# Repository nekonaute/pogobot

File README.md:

# Pogobot

## Overview 
The pogobot is a small robot designed for swarm robotics experiments, targeted at collective behaviour and social learning research.
The robot is composed of a head (above) with a iCE40UP5K FPGA chip including a softcore processor, an IMU, fast Infra-Red communication devices and a LED.
The head is plugged on a belly (under) which composed of even more LEDs, the motor controler, the battery and the battery regulation system.

To help the understanding, there is two version names used inside the project, one for the hardware and one for the software. <br> 
The following table gives an overview :

| hardware version | software version | comments                                                                             |
|:----------------:|:----------------:|--------------------------------------------------------------------------------------|
|        V3        |        V1        | initial version                                                                      |
|        V3        |        V2        | reduce communication speed to increase reliability                                   |
|        V3        |       V2.1       | reduce header footprint                                                              |
|        V3        |       V2.2       | introduce short message and clean the pogobios                                       |
|        V3        |      V2.2.1      | fix the IR programation problem                                                      |
|        V3        |       V2.3       | API standardization : motor                                                          |
|        V3        |       V2.4       | API standardization : IR messaging                                                   |
|        V3        |       V2.5       | new API standardization : IR messaging                                               |
|        V3        |       V2.6       | new API standardization : IR messaging                                               |
|        V3        |       V2.7       | fix IR saturation at startup, add user access to the flash memory, add magnetometer  |

## Git description
This project is divided into 3 folders :
- Hardware
- Software
- Tools

Hardware contains the schematics and other files to build your own robot from scratch. 

All the schematics were done using KiCad 6. You can find : 
- 'Belly' folder with the belly schematics
- 'Head' folder with the head schematics
- '3d-addons' folder contains all the 3D parts to print to complete a robot
- '3Dmodels' and other folders regroups all the libraries, 3D models and foorprints for KiCad.
   
Software contains the gateware / software / SDK builder in expert mode to upload inside the robot.
It exists 2 softwares inside the robot. 
- The bootloader is the one called when you boot the robot. It contains a gateware and the pogobios.
- The user space is called by a command inside the bootloader. It contains your code and a gateware. <br>
/!\ If you plan to use the pogobot in the user space please use the sdk [here](https://github.com/nekonaute/pogobot-sdk).
  
Tools corresponds to the differents tools used around the robot.

### Shortcuts to

- [Normal mode software](https://github.com/nekonaute/pogobot-sdk)
- [Expert mode software](/Software/readme.md)
- [Hardware](/Hardware/readme.md)
- [Ir Remote software](/readme-irRemote.md)
- [Charger](/Hardware/readme.md)
- [Pogobject](/Software/pogobject/readme.md)
- [PogoWallApp](/Software/pogoWallApp/readme.md)

## Pogobios LED Status

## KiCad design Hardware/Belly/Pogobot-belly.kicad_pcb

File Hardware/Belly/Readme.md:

# Belly
Belly board (Kicad project) to use with head board (pogobot v2).
Holds the battery, battery charger, motors, ...

## Belly v2
file : bellyv2

## Belly V3
file : pogobot_belly

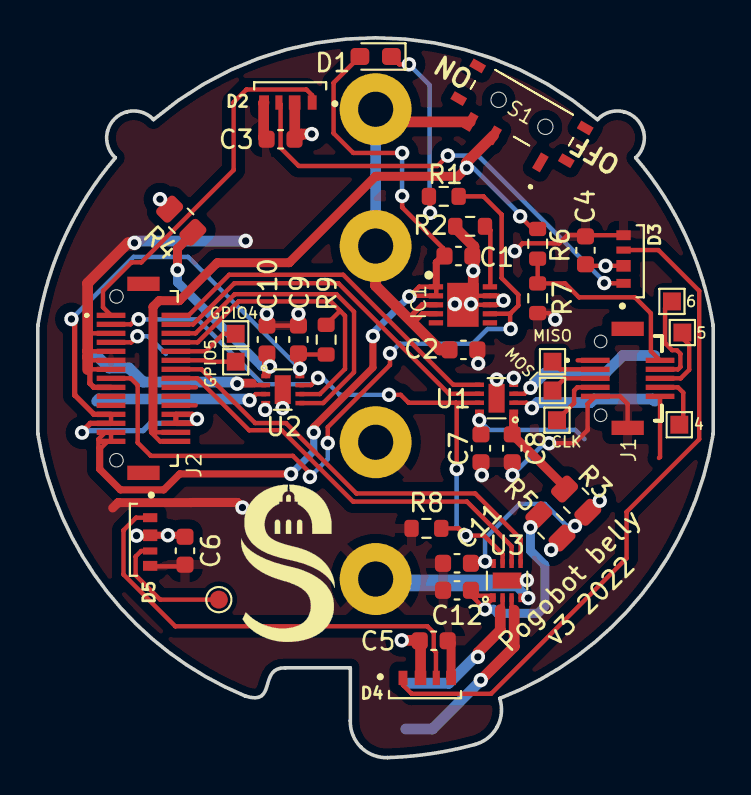
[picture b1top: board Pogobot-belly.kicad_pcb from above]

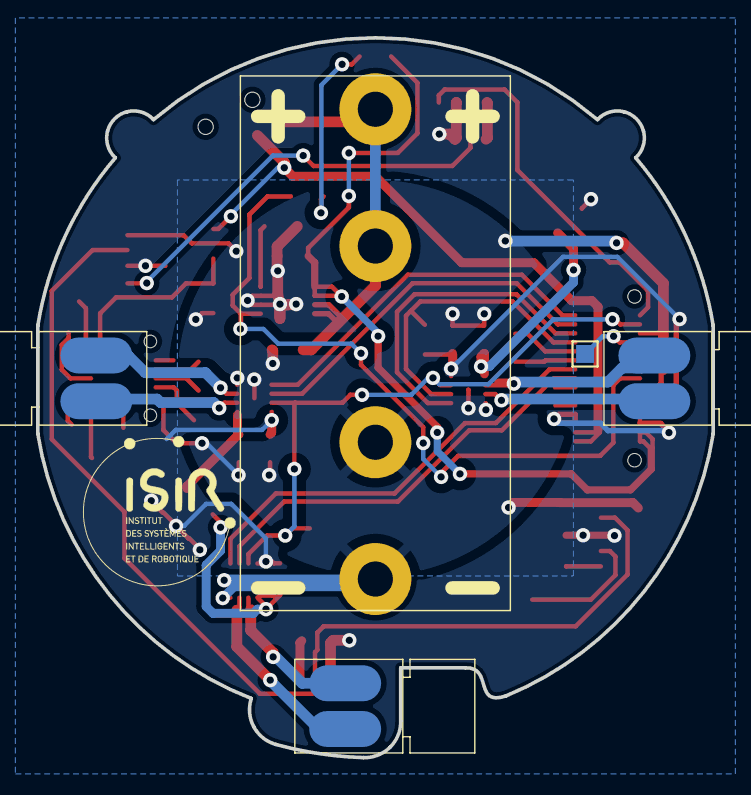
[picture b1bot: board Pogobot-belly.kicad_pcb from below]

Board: 2 copper layers, 37.5 x 40.0 mm, 47 parts (5 on the bottom side), 39 nets.

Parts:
4, 5, 6: TestPoint; TestPoint_Pad_1.0x1.0mm
C1, C2: 4.7uF; C_0603_1608Metric
C3, C4, C5, C6: 1uF; C_0603_1608Metric
C7, C8, C9, C10, C11, C12: 100n; C_0603_1608Metric
CLK: TestPoint; TestPoint_Pad_1.0x1.0mm
D1: LED; LED_0603_1608Metric_Pad1.05x0.95mm_HandSolder
D2, D3, D4, D5: IN-PI42TASPRPGPB; LED_IN-PI42TASPRPGPB
GPIO4, GPIO5: TestPoint; TestPoint_Pad_1.0x1.0mm
IC1: MCP73123-22SI_MF; SON50P300X300X100-11N-D
J1: 10132797-015100LF; 10132797015100LF
J2: 10132797-035100LF; 10132797035100LF
J3: CR2 Battery Holder; CR2_Holder
M1, M2, M3: Motor_DC; Vibrating_5x6mm_DC_motor
MISO: TestPoint; TestPoint_Pad_1.0x1.0mm
MOSI: TestPoint; TestPoint_Pad_1.0x1.0mm
R1: 1K; R_0603_1608Metric
R2, R6, R7, R8, R9: 10K; R_0603_1608Metric
R3, R4, R5: 0; R_0805_2012Metric
S1: MSK12C02
TP1: TestPoint; TestPoint_Pad_1.0x1.0mm
TP4: RGB_Out; TestPoint_Pad_D1.0mm
U1, U2, U3: DRV8837C; WSON-8-1EP_2x2mm_P0.5mm_EP0.9x1.6mm

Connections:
+3V3: C3.1, C4.1, C5.1, C6.1, C7.1, C9.1, C11.1, D2.2 (VDD), D3.2 (VDD), D4.2 (VDD), D5.2 (VDD), J2.12, J2.13, J2.18, J2.19, R3.1, R4.1, R5.1, R9.1, U1.8 (VCC), U2.8 (VCC), U3.8 (VCC)
+5V: C1.1, D1.2 (A), IC1.1 (VDD_1), IC1.2 (VDD_2), J2.14, J2.15
+BATT: J2.16, J2.17, R6.1, S1.B1 (COM)
/CH4: 4.1, J1.7
/CH5: 5.1, J1.8
/CH6: 6.1, J1.9
/CH7: J1.10, R6.2, R7.1
/prog: IC1.10 (PROG), R2.2
CDONE: J2.4, TP1.1
GND: C1.2, C2.2, C3.2, C4.2, C5.2, C6.2, C7.2, C8.2, C9.2, C10.2, C11.2, C12.2, D2.4 (GND), D3.4 (GND), D4.4 (GND), D5.4 (GND), IC1.8 (VSS_1), IC1.9 (VSS_2), IC1.11 (EP), J1.5, J1.MP2, J2.3, J2.5, J2.6, J2.7, J2.9, J3.2, R2.1, R7.2, R8.2, U1.4 (GND), U1.9 (GND), U2.4 (GND), U2.9 (GND), U3.4 (GND), U3.9 (GND)
GPIO0: J2.30, U1.5 (IN2)
GPIO1: J2.29, U1.6 (IN1)
GPIO2: J2.28, U2.5 (IN2)
GPIO3: J2.27, R9.2, U2.6 (IN1)
GPIO4: GPIO4.1, J2.26
GPIO5: GPIO5.1, J2.25
GPIO6: J2.24, U3.5 (IN2)
GPIO7: J2.23, U3.6 (IN1)
GPIO8: J2.2, R8.1, U1.7 (~SLEEP), U2.7 (~SLEEP), U3.7 (~SLEEP)
LED_CHARGE: IC1.7 (STAT), J2.8, R1.2
unnamed: C2.1, IC1.3 (VBAT_1), IC1.4 (VBAT_2), J3.1, S1.C1 (NO)
unnamed: C8.1, R3.2, U1.1 (VM)
unnamed: C10.1, R4.2, U2.1 (VM)
unnamed: C12.1, R5.2, U3.1 (VM)
unnamed: D1.1 (K), R1.1
unnamed: D2.3 (DOUT), D3.1 (DIN)
unnamed: D3.3 (DOUT), D4.1 (DIN)
unnamed: D4.3 (DOUT), D5.1 (DIN)
unnamed: D5.3 (DOUT), TP4.1
unnamed: M1.1 (+), U1.2 (OUT1)
unnamed: M1.2 (-), U1.3 (OUT2)
unnamed: M2.1 (+), U2.2 (OUT1)
unnamed: M2.2 (-), U2.3 (OUT2)
unnamed: M3.1 (+), U3.2 (OUT1)
unnamed: M3.2 (-), U3.3 (OUT2)
RGB_LED_OUT: D2.1 (DIN), J2.1
SPI_CLK: CLK.1, J1.4
SPI_MISO: J1.2, MISO.1
SPI_MOSI: J1.3, MOSI.1

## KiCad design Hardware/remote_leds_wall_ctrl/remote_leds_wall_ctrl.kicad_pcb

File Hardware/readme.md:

# Hardware
Here you can find the description and information for each part developped.

<!-- vscode-markdown-toc -->
- [Hardware](#hardware)
  - [Folder description](#folder-description)
  - [Pogobot robot](#pogobot-robot)
    - [Hardware schematic](#hardware-schematic)
    - [What's needed for 1 robot](#whats-needed-for-1-robot)
    - [Motor information](#motor-information)
    - [3d printed parts](#3d-printed-parts)
      - [Printing info](#printing-info)
      - [Assembly](#assembly)
  - [USB UART progboard](#usb-uart-progboard)
  - [Charger](#charger)
  - [IR remote](#ir-remote)
  - [IR Wall](#ir-wall)
  - [Pogobject](#pogobject)

<!-- vscode-markdown-toc-config
	numbering=false
	autoSave=true
	/vscode-markdown-toc-config -->
<!-- /vscode-markdown-toc -->

## Folder description
In this folder, you can find 3d models and kicad files.

The folder :
- "3d-addons" contains all the STL files to build the different object.
- "3Dmodels" contains the 3D models for Kicad
- 'Belly" contains the kicad files for the belly
- "Charger" contains the kicad files for the charger
- "Footprints.pretty" is the Kicad library for custom footprints
- "Head" contains the kicad files for the head
- "pogo_object" contains the kicad files for the pogobject
- "remote" contains the kicad files for the board which host the head of a remote
- "remote_leds_strip" contains the kicad files for the "shower" part of a remote
- "remote_leds_wall_ctrl" contains the kicad files for the amplification signal for a led strip
- "remote_leds_wall_strip" contains the kicad files for the strip leds of a wall remote
- "Symbols" contains the custom symbols for kicad
- "usb-uart-progboard" contains the kicad files for the programmation board by cable

## Pogobot robot

### Hardware schematic
Here you can find the global view of the hardware.

### What's needed for 1 robot

In order to complete a robot, you will need : 
- a belly and a head
- a 3v CR2 rechargeable Batery (Li-FePO4)
- 3 motors
- the different 3d printed parts

### Motor information
All the models are designed for the motors available here:
<!-- https://www.aliexpress.com/item/32918768766.html old ref -->
https://www.ebay.com/itm/115374108208

### 3d printed parts
All the parts are available inside the folder 'Hardware/3d-addons'.

#### Printing info
The different models have been printed in PLA with an Ultimaker2+ with a layer height of 0.2mm without support or brim.

To assemble a robot, you need to print a skirt, a capsule and a hat for the version of your belly. <br>
After printed the capsule, you have to set free the tabs by gently cut under.

HINT: The hat has to be returned to be printed without support.

#### Assembly
- First, place the motors inside the 3 holes.
- Then, place the robot inside the capsule.
- Finally, place the robot+capsule inside the skirt.

## USB UART progboard
In order to program the robot by cable, you need a USB to UART device connected between your computor and the FFC/FPC connector on the head. 
The folder 'Hardware/usb-uart-progboard' contains the Kicad files to produce a small board to program the robot. 
You also need :
- UMFT234XF board (https://www.mouser.fr/ProductDetail/FTDI/UMFT234XF?qs=NVftvxkm2thPJLzIkoAhbA%3D%3D)
- a FFC/FPC connector (8 pins, 0.5 mm, SMD/SMT, Right Angle, Dual Contact) like https://www.mouser.fr/ProductDetail/571-2328702-8
- a FFC/FPC cable (8 pins, 0.5 mm) like https://www.mouser.fr/ProductDetail/538-15166-0087
- a USB micro => USB cable

## Charger
There is two ways to recharge a pogobot:
- by the programming cable
- by the plus and minus pads on the head

In order to charge multiple robot at once, we develop a charger using pogopins that connect the plus and minus on the head of the robot by flipping the robot.

The PCB cad files are available in the folder.
The pogopin used are these : https://www.digikey.fr/en/products/detail/preci-dip/90224-AS/5451911
We also used one power jack 5.1 embase connected to the power outlet. The second one is used, if you want to daisy chain multiple PCB (be careful, the total amps used).
:warning: The power plug has to expose the +5v on the inner contact and Ground on the outer contact. Please verify with a voltmeter before pluggin a robot.

We developed some small feet to mount with M3 screws on the PCB and some small cones in order to help the contacts for each robot.
Both 3d designs are available in the folder "3d-addons" (pogocharger*).

## IR remote
2 types of IR remote are possible. A small one and one with a shower. 

The small one is combination of a pogobot head + usb-uart-progboard + 3D structure (pogoremote_down.stl + pogoremote_up.stl) + 2 M3x10mm screws.

The big one is combination of a pogobot head + remote + remote_Leds_strip + 3D structure

The leds are TSAL6200.

This version can use the USB alimentation or an external one (up to 12v) to extend the range of the remote. The jumper near the power jack determine the origin of the tension for the Leds.

## IR Wall 

The IR wall is a modified remote that can connect a long strip of Leds.
We didn't manage to find the correct Led strip for our application so we designed a strip led (remote_leds_wall_strip) that was produiced on flexible pcb. 

To produice a IR wall, you need a pogobot head + remote + remote_leds_wall_ctrl + remote_leds_wall_strip. 

The leds are VSM3940x01.

## Pogobject

The pogobject is composed of a dfrobot firebeatle + pogobot head + pogo_object PCB. Through WIFI, it can be possible to send command to the pogobot head and so to change the message send by the object.

The pogobject is a large PCB that contains all the electronics. It is placed inside a 3d printed structure. This structure is placed on 4 caster with metal ball (pololu item 953) in order to be pushed by the robot. To make it fixed a aluminum weight is used to held it in place. 

The leds are TSAL6200.

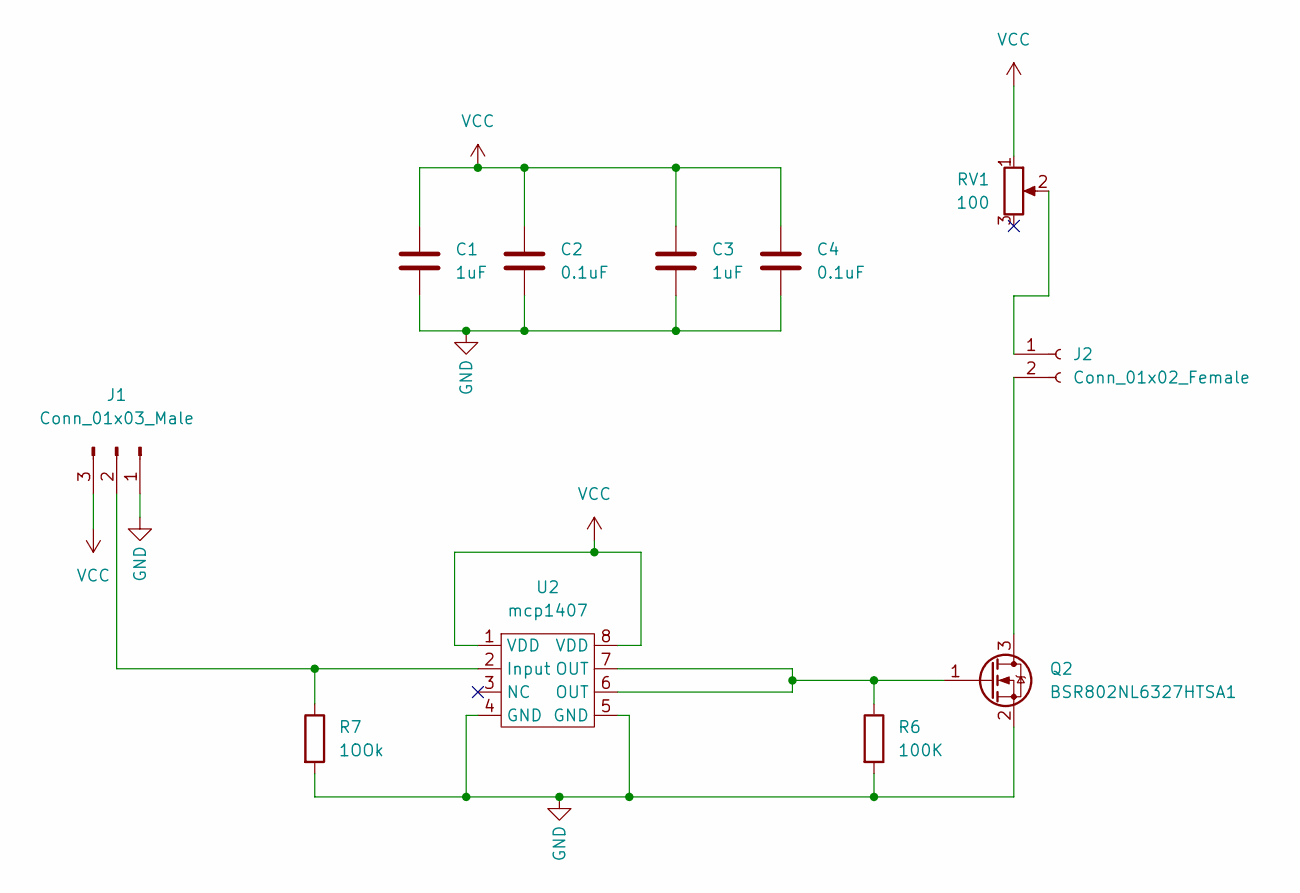
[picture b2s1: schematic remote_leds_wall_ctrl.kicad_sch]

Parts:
C1: 1uF; C_0805_2012Metric_Pad1.18x1.45mm_HandSolder
C2: 0.1uF; C_0805_2012Metric_Pad1.18x1.45mm_HandSolder
C3: 1uF; CP_Radial_D5.0mm_P2.00mm
C4: 0.1uF; CP_Radial_D5.0mm_P2.00mm
J1: Conn_01x03_Male; PinHeader_1x03_P2.54mm_Vertical
J2: Conn_01x02_Female; PinHeader_1x02_P2.54mm_Vertical
Q2: BSR802NL6327HTSA1; SOT-23
R6: 100K; R_0805_2012Metric_Pad1.20x1.40mm_HandSolder
R7: 1OOk; R_0805_2012Metric_Pad1.20x1.40mm_HandSolder
RV1: 100; PinHeader_1x03_P2.54mm_Vertical
U2: mcp1407; SOIC-8_3.9x4.9mm_P1.27mm

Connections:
GND: C1.2, C2.2, C3.2, C4.2, J1.1, Q2.2 (S), R6.2, R7.2, U2.4 (GND), U2.5 (GND)
unnamed: J1.2, R7.1, U2.2 (Input)
unnamed: J2.1, RV1.2
unnamed: J2.2, Q2.3 (D)
unnamed: Q2.1 (G), R6.1, U2.6 (OUT), U2.7 (OUT)
VCC: C1.1, C2.1, C3.1, C4.1, J1.3, RV1.1, U2.1 (VDD), U2.8 (VDD)

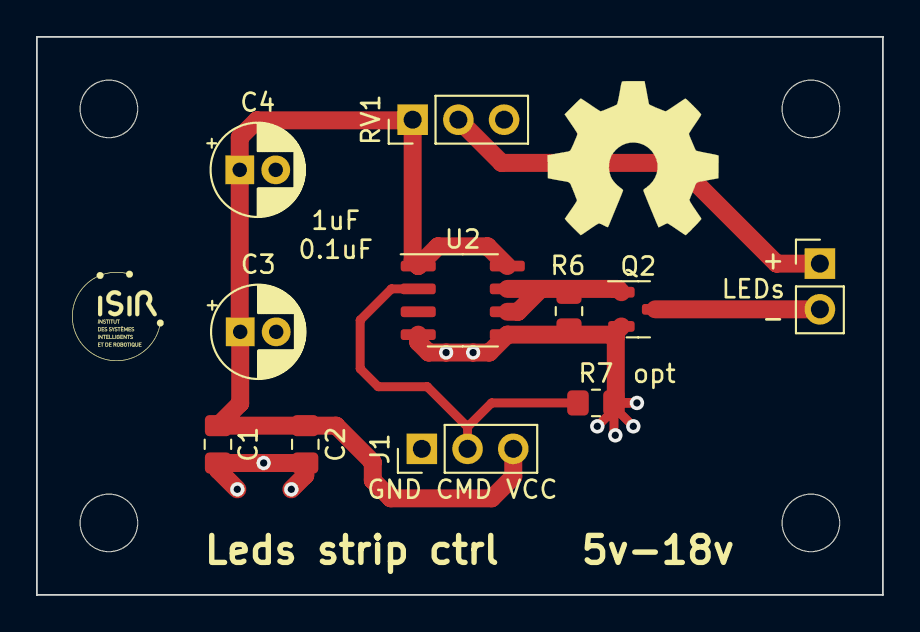
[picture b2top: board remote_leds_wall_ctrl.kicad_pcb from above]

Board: 2 copper layers, 47.0 x 31.0 mm, 11 parts (0 on the bottom side), 6 nets.

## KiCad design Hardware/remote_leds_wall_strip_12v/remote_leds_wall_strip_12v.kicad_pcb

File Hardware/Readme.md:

# Hardware
Here you can find the description and information for each part developped.

<!-- vscode-markdown-toc -->
- [Hardware](#hardware)
  - [Folder description](#folder-description)
  - [Pogobot robot](#pogobot-robot)
    - [Hardware schematic](#hardware-schematic)
    - [What's needed for 1 robot](#whats-needed-for-1-robot)
    - [Motor information](#motor-information)
    - [3d printed parts](#3d-printed-parts)
  - [USB UART progboard](#usb-uart-progboard)
  - [Charger](#charger)
  - [IR remote](#ir-remote)
  - [IR Wall](#ir-wall)
  - [Pogobject](#pogobject)

<!-- vscode-markdown-toc-config
	numbering=false
	autoSave=true
	/vscode-markdown-toc-config -->
<!-- /vscode-markdown-toc -->

## Folder description
In this folder, you can find 3d models and kicad files.

The folder :
- "3Dmodels" contains the 3D models for Kicad
- 'Belly" contains the kicad files for the belly
- "Charger" contains the kicad files for the charger
- "Footprints.pretty" is the Kicad library for custom footprints
- "Head" contains the kicad files for the head
- "pogo_object" contains the kicad files for the pogobject
- "remote" contains the kicad files for the board which host the head of a remote
- "remote_leds_strip" contains the kicad files for the "shower" part of a remote
- "remote_leds_wall_ctrl" contains the kicad files for the amplification signal for a led strip
- "remote_leds_wall_strip" contains the kicad files for the strip leds of a wall remote
- "Symbols" contains the custom symbols for kicad
- "usb-uart-progboard" contains the kicad files for the programmation board by cable

## Pogobot robot

### Hardware schematic
Here you can find the global view of the hardware.

### What's needed for 1 robot

In order to complete a robot, you will need : 
- a belly and a head
- a 3v CR2 rechargeable Batery (Li-FePO4)
- 3 motors
- the different 3d printed parts

### Motor information
All the models are designed for the motors available here:
<!-- https://www.aliexpress.com/item/32918768766.html old ref -->
https://www.ebay.com/itm/115374108208

### 3d printed parts
All the parts are available inside the folder '3d-addons', along with [assembly instructions](../3d-addons/Readme.md).

## USB UART progboard
In order to program the robot by cable, you need a USB to UART device connected between your computor and the FFC/FPC connector on the head. 
The folder 'Hardware/usb-uart-progboard' contains the Kicad files to produce a small board to program the robot. 
You also need :
- UMFT234XF board (https://www.mouser.fr/ProductDetail/FTDI/UMFT234XF?qs=NVftvxkm2thPJLzIkoAhbA%3D%3D)
- a FFC/FPC connector (8 pins, 0.5 mm, SMD/SMT, Right Angle, Dual Contact) like https://www.mouser.fr/ProductDetail/571-2328702-8
- a FFC/FPC cable (8 pins, 0.5 mm) like https://www.mouser.fr/ProductDetail/538-15166-0087
- a USB micro => USB cable

## Charger
There is two ways to recharge a pogobot:
- by the programming cable
- by the plus and minus pads on the head

In order to charge multiple robot at once, we develop a charger using pogopins that connect the plus and minus on the head of the robot by flipping the robot.

The PCB cad files are available in the folder.
The pogopin used are these : https://www.digikey.fr/en/products/detail/preci-dip/90224-AS/5451911
We also used one power jack 5.1 embase connected to the power outlet. The second one is used, if you want to daisy chain multiple PCB (be careful, the total amps used).
:warning: The power plug has to expose the +5v on the inner contact and Ground on the outer contact. Please verify with a voltmeter before pluggin a robot.

We developed some small feet to mount with M3 screws on the PCB and some small cones in order to help the contacts for each robot.
Both 3d designs are available in the folder "3d-addons" (pogocharger*).

## IR remote
2 types of IR remote are possible. A small one and one with a shower. 

The small one is combination of a pogobot head + usb-uart-progboard + 3D structure (pogoremote_down.stl + pogoremote_up.stl) + 2 M3x10mm screws.

The big one is combination of a pogobot head + remote + remote_Leds_strip + 3D structure

The leds are TSAL6200.

This version can use the USB alimentation or an external one (up to 12v) to extend the range of the remote. The jumper near the power jack determine the origin of the tension for the Leds.

## IR Wall 

The IR wall is a modified remote that can connect a long strip of Leds.
We didn't manage to find the correct Led strip for our application so we designed a strip led (remote_leds_wall_strip) that was produiced on flexible pcb. 

To produice a IR wall, you need a pogobot head + remote + remote_leds_wall_ctrl + remote_leds_wall_strip. 

The leds are VSM3940x01.

## Pogobject

The pogobject is composed of a dfrobot firebeatle + pogobot head + pogo_object PCB. Through WIFI, it can be possible to send command to the pogobot head and so to change the message send by the object.

The pogobject is a large PCB that contains all the electronics. It is placed inside a 3d printed structure. This structure is placed on 4 caster with metal ball (pololu item 953) in order to be pushed by the robot. To make it fixed a aluminum weight is used to held it in place. 

The leds are TSAL6200.

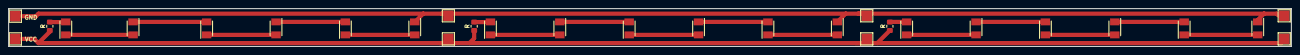
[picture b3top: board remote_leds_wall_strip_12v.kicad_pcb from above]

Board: 2 copper layers, 305.1 x 9.0 mm, 29 parts (0 on the bottom side), 20 nets.

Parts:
L1, L2, L3, L4, L5, L6, L7, L8, L9, L10, L11, L12, L13, L14, L15, L16, L17, L18: VSMB3940X01-GS08; LEDM3528X185N
R: 15; R_0805_2012Metric_Pad1.20x1.40mm_HandSolder
R#2, R#3: 15; R_0805_2012Metric_Pad1.20x1.40mm_HandSolder
TP1, TP2, TP3, TP4, TP5, TP6, TP12, TP27: TestPoint; TestPoint_Pad_2.5x2.5mm

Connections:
GND: L4.1 (K), L10.1 (K), L16.1 (K), TP1.1, TP3.1, TP6.1, TP12.1
unnamed: L1.1 (K), L2.2 (A)
unnamed: L1.2 (A), L18.1 (K)
unnamed: L2.1 (K), L3.2 (A)
unnamed: L3.1 (K), L4.2 (A)
unnamed: L5.1 (K), L6.2 (A)
unnamed: L5.2 (A), R#3.2
unnamed: L6.1 (K), L7.2 (A)
unnamed: L7.1 (K), L8.2 (A)
unnamed: L8.1 (K), L9.2 (A)
unnamed: L9.1 (K), L10.2 (A)
unnamed: L11.1 (K), L12.2 (A)
unnamed: L11.2 (A), R.2
unnamed: L12.1 (K), L13.2 (A)
unnamed: L13.1 (K), L14.2 (A)
unnamed: L14.1 (K), L15.2 (A)
unnamed: L15.1 (K), L16.2 (A)
unnamed: L17.1 (K), L18.2 (A)
unnamed: L17.2 (A), R#2.2
VCC: R.1, R#2.1, R#3.1, TP2.1, TP4.1, TP5.1, TP27.1

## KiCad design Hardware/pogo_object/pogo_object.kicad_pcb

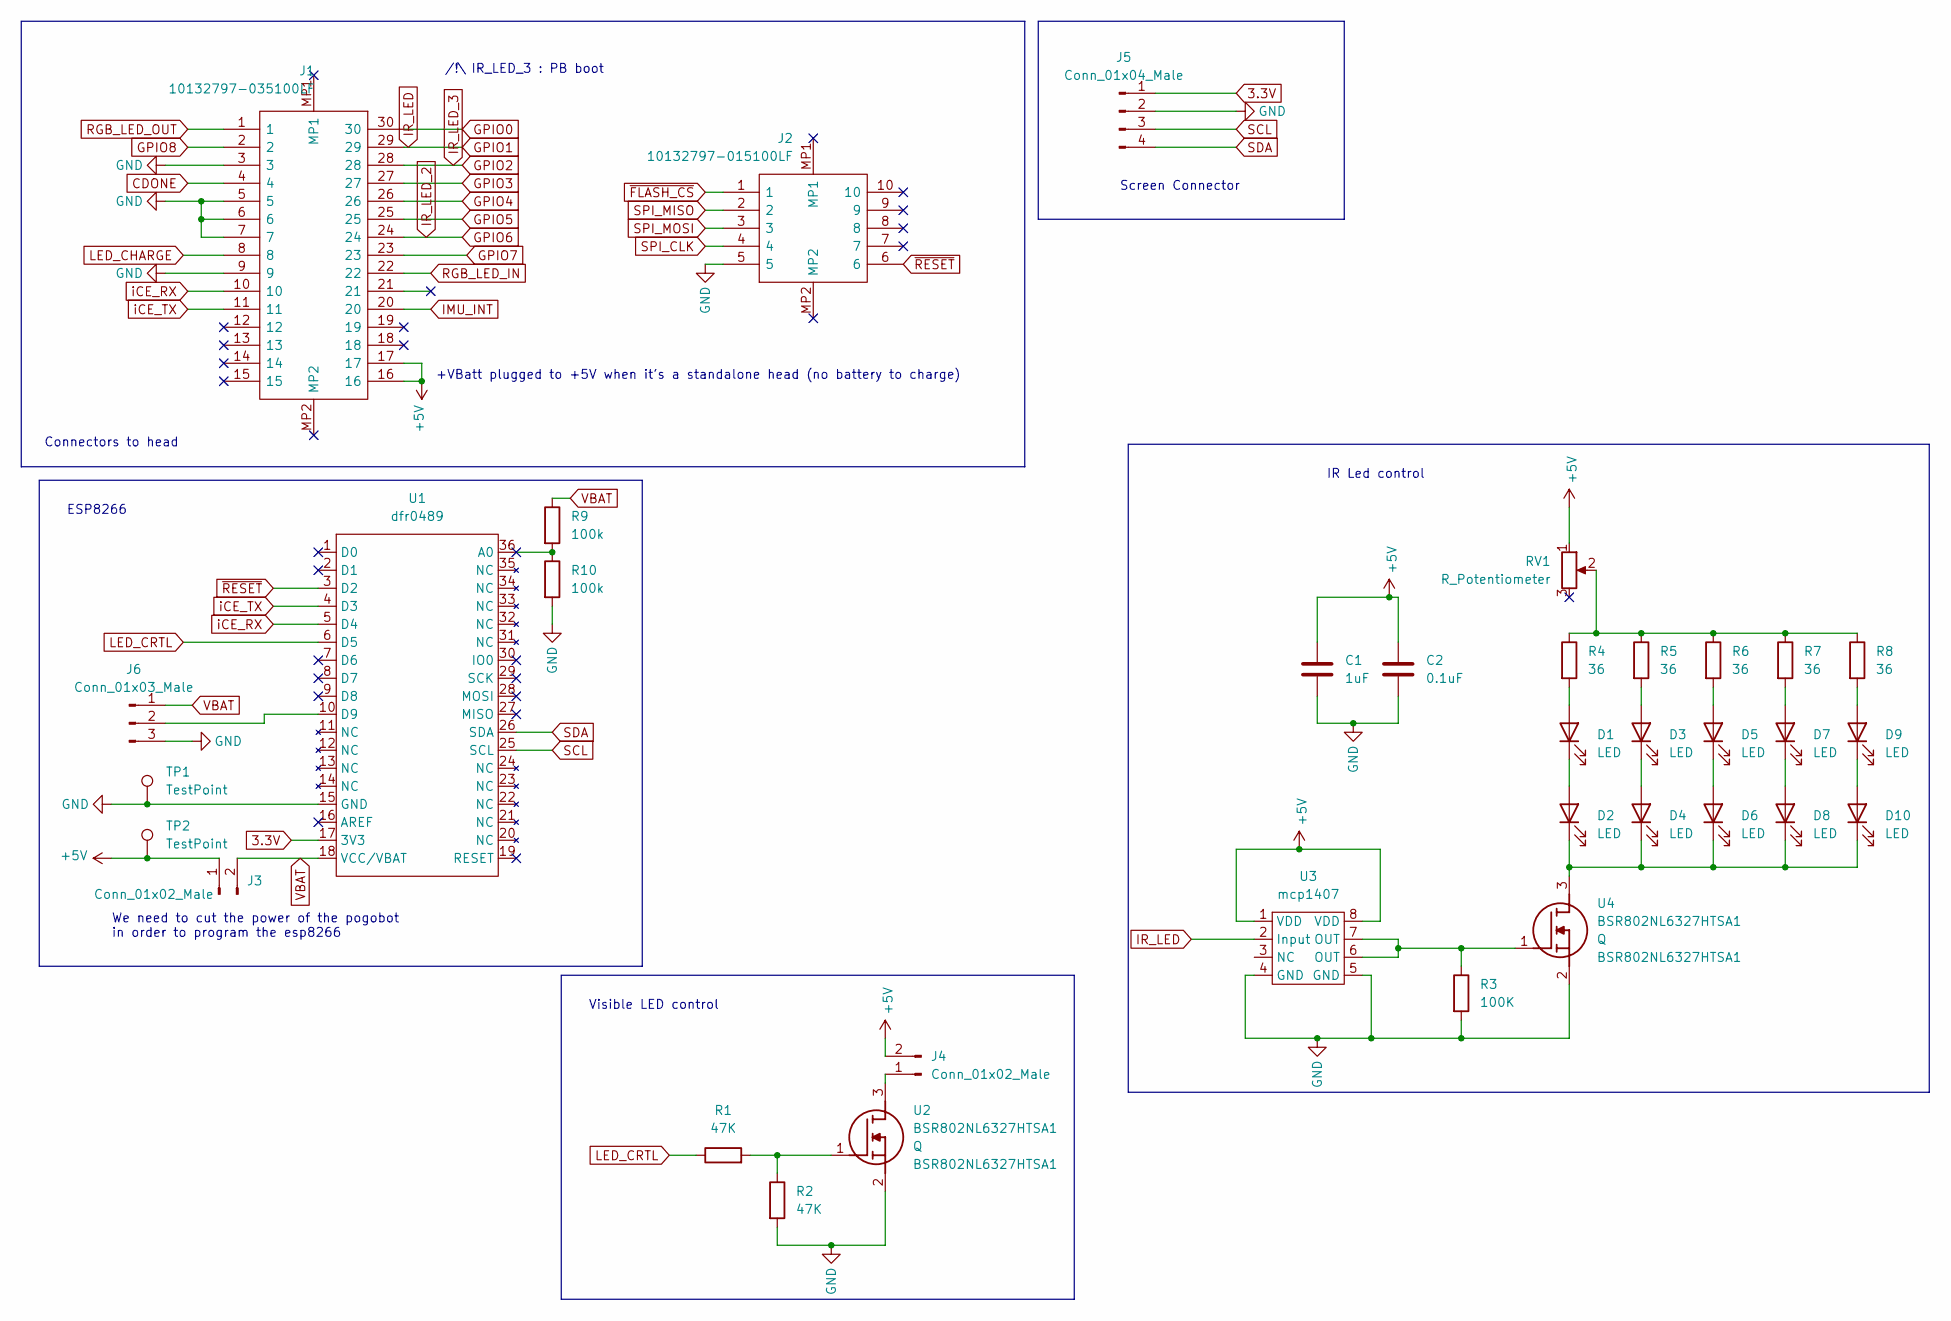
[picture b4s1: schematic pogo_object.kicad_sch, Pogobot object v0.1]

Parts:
C1: 1uF; CP_Radial_D8.0mm_P5.00mm
C2: 0.1uF; CP_Radial_D8.0mm_P5.00mm
D1, D2, D3, D4, D5, D6, D7, D8, D9, D10: LED; D_A-405_P2.54mm_Vertical_AnodeUp
J1: 10132797-035100LF; 10132797035100LF; Manufacturer_Part_Number 10132797-035100LF; Mouser Part Number 649-10132797035100LF
J2: 10132797-015100LF; 10132797015100LF; Manufacturer_Part_Number 10132797-015100LF; Mouser Part Number 649-10132797015100LF
J3, J4: Conn_01x02_Male; PinHeader_1x02_P2.54mm_Vertical
J5: Conn_01x04_Male; PinHeader_1x04_P2.54mm_Vertical
J6: Conn_01x03_Male; PinHeader_1x03_P2.54mm_Vertical
R1, R2: 47K; R_0805_2012Metric_Pad1.20x1.40mm_HandSolder
R3: 100K; R_0805_2012Metric_Pad1.20x1.40mm_HandSolder
R4, R5, R6, R7, R8: 36; R_0805_2012Metric_Pad1.20x1.40mm_HandSolder
R9, R10: 100k; R_0805_2012Metric_Pad1.20x1.40mm_HandSolder
RV1: R_Potentiometer; PinHeader_1x03_P2.54mm_Vertical
TP1, TP2: TestPoint; TestPoint_Pad_3.0x3.0mm
U1: dfr0489
U2, U4: BSR802NL6327HTSA1; SOT95P285X135-3N; Mouser Part Number 726-BSR802NL6327HTSA
U3: mcp1407; SOIC-8_3.9x4.9mm_P1.27mm

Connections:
3.3V: J5.1, U1.17 (3V3)
+5V: C1.1, C2.1, J1.16, J1.17, J3.1, J4.2, RV1.1, TP2.1, U3.1 (VDD), U3.8 (VDD)
CDONE: J1.4
GND: C1.2, C2.2, J1.3, J1.5, J1.6, J1.7, J1.9, J2.5, J5.2, J6.3, R2.2, R3.2, R10.2, TP1.1, U1.15 (GND), U2.2 (S), U3.4 (GND), U3.5 (GND), U4.2 (S)
GPIO0: J1.30
GPIO1: J1.29, U3.2 (Input)
GPIO2: J1.28
GPIO3: J1.27
GPIO4: J1.26
GPIO5: J1.25
GPIO6: J1.24
GPIO7: J1.23
GPIO8: J1.2
IMU_INT: J1.20
LED_CHARGE: J1.8
LED_CRTL: R1.1, U1.6 (D5)
unnamed: D1.1 (K), D2.2 (A)
unnamed: D1.2 (A), R4.2
unnamed: D3.1 (K), D4.2 (A)
unnamed: D3.2 (A), R5.2
unnamed: D5.1 (K), D6.2 (A)
unnamed: D5.2 (A), R6.2
unnamed: D7.1 (K), D8.2 (A)
unnamed: D7.2 (A), R7.2
unnamed: D9.2 (A), R8.2
unnamed: D2.1 (K), D4.1 (K), D6.1 (K), D8.1 (K), D10.1 (K), U4.3 (D)
unnamed: D9.1 (K), D10.2 (A)
unnamed: J4.1, U2.3 (D)
unnamed: R1.2, R2.1, U2.1 (G)
unnamed: R3.1, U3.6 (OUT), U3.7 (OUT), U4.1 (G)
unnamed: R4.1, R5.1, R6.1, R7.1, R8.1, RV1.2
unnamed: J6.2, U1.10 (D9)
RGB_LED_IN: J1.22
RGB_LED_OUT: J1.1
SCL: J5.3, U1.25 (SCL)
SDA: J5.4, U1.26 (SDA)
SPI_CLK: J2.4
SPI_MISO: J2.2
SPI_MOSI: J2.3
VBAT: J3.2, J6.1, R9.1, U1.18 (VCC/VBAT)
iCE_RX: J1.10, U1.5 (D4)
iCE_TX: J1.11, U1.4 (D3)
~FLASH_CS: J2.1
~RESET: J2.6, U1.3 (D2)

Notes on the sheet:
Connectors to head
Screen Connector
IR Led control
/!\ IR_LED_3 : PB boot
We need to cut the power of the pogobot in order to program the esp8266
Visible LED control
ESP8266
+VBatt plugged to +5V when it's a standalone head (no battery to charge)

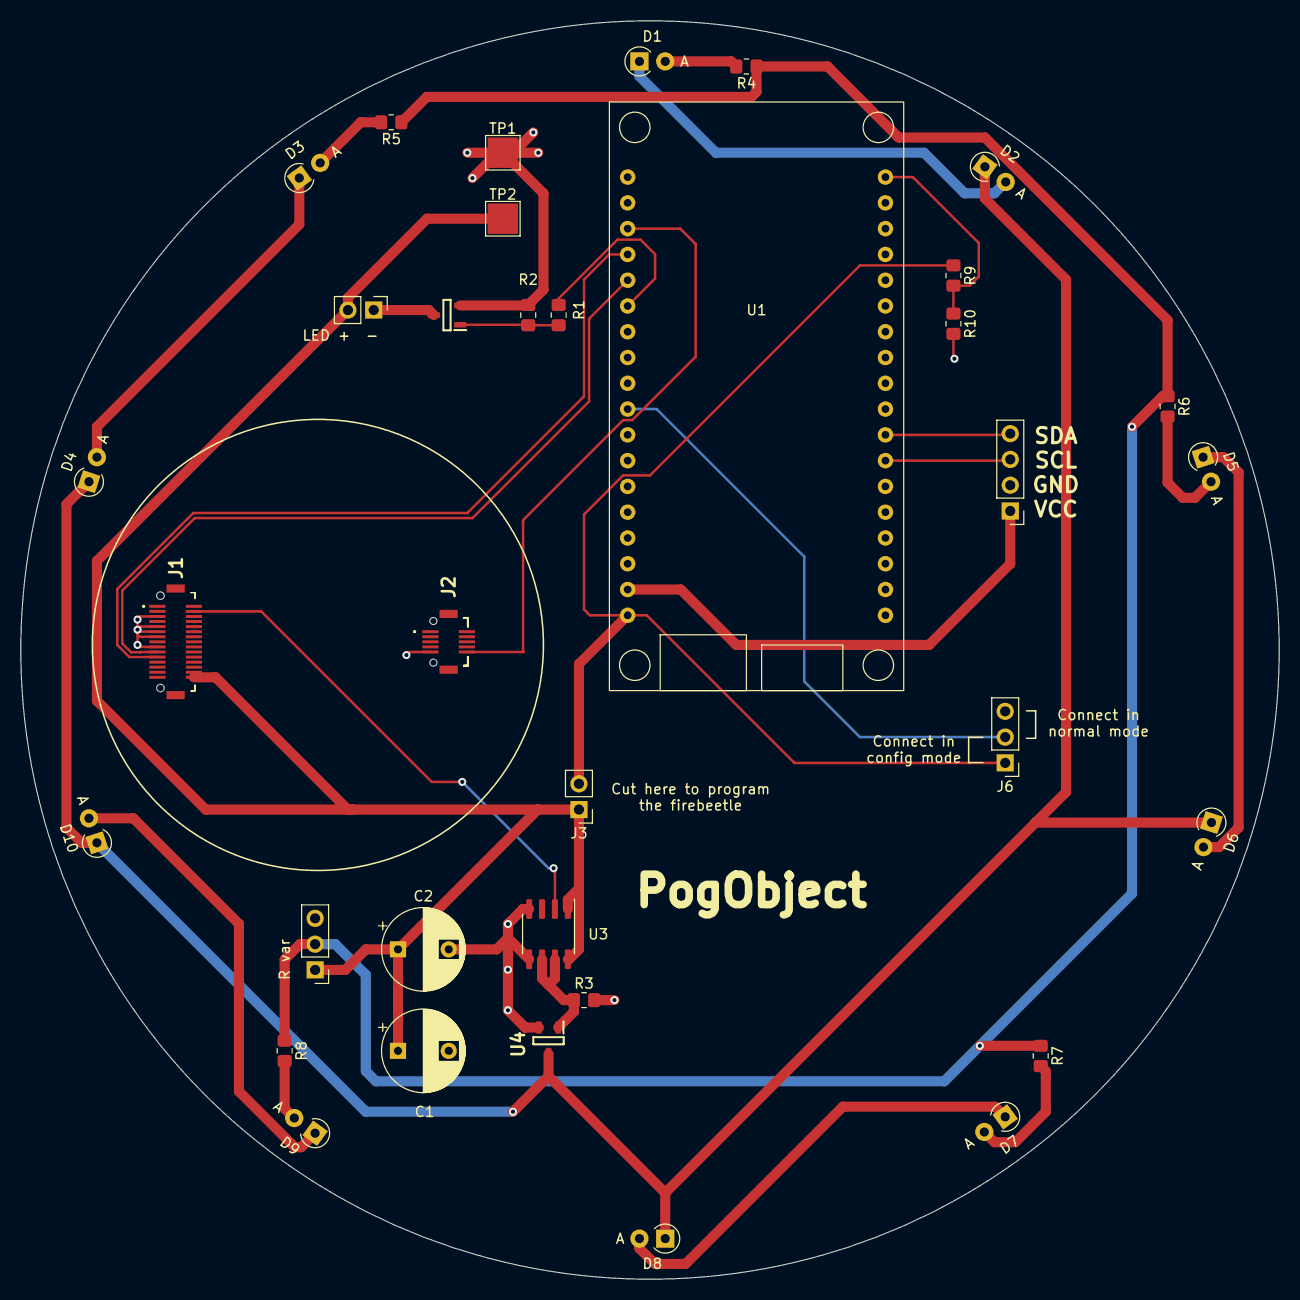
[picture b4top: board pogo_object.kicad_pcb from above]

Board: 2 copper layers, 124.0 x 124.0 mm, 35 parts (0 on the bottom side), 27 nets.

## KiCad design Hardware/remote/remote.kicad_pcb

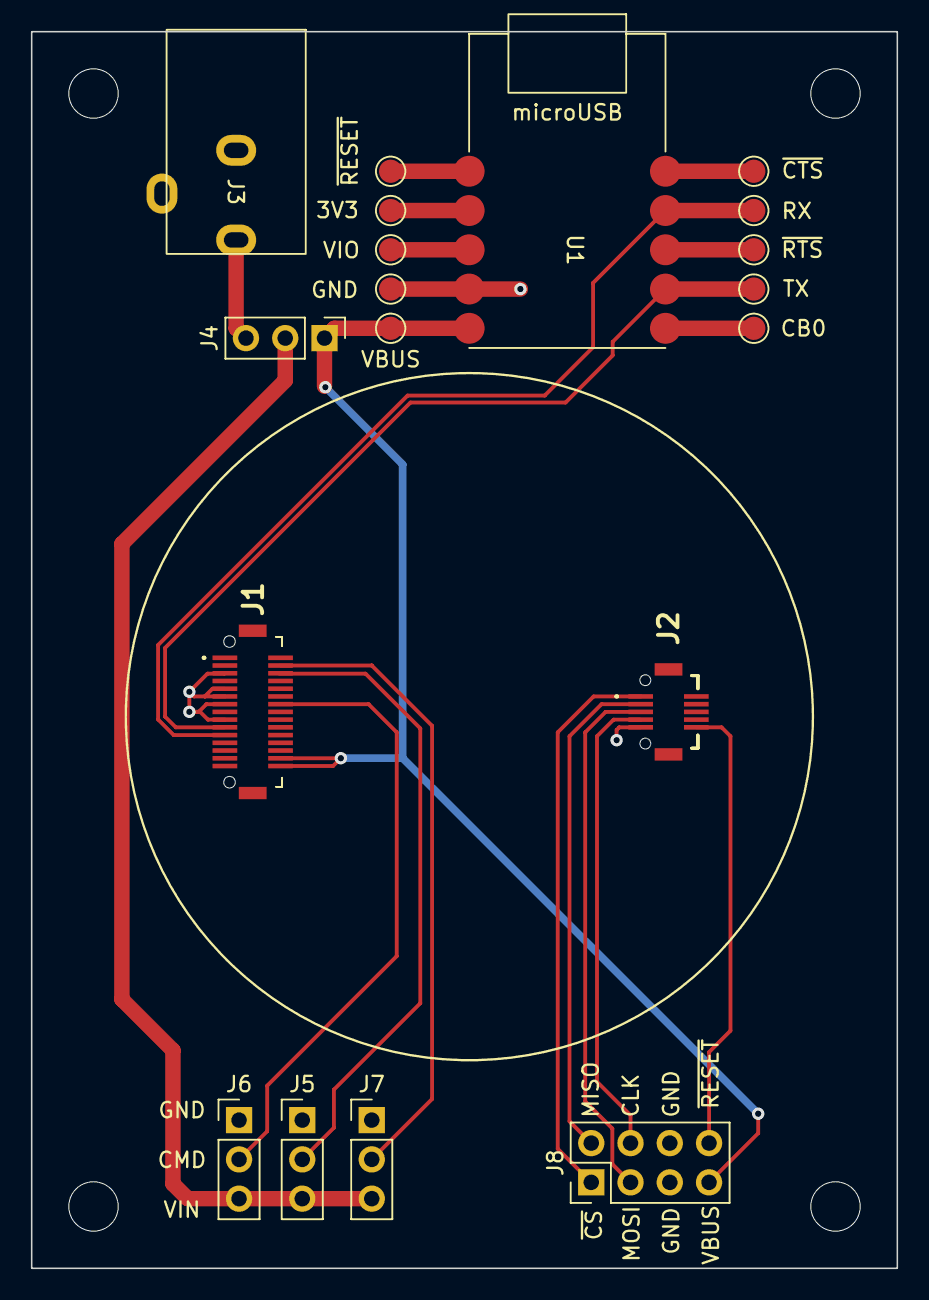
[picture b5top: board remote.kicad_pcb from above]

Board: 2 copper layers, 56.0 x 80.0 mm, 16 parts (0 on the bottom side), 17 nets.

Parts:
3V3: TestPoint; TestPoint_Pad_D1.5mm
CB0: TestPoint; TestPoint_Pad_D1.5mm
GND: TestPoint; TestPoint_Pad_D1.5mm
J1: 10132797-035100LF; 10132797035100LF
J2: 10132797-015100LF; 10132797015100LF
J3: Barrel_Jack_Switch; Barrel Jack_SparkFun_PRT-10811
J4, J5, J6, J7: Conn_01x03_Male; PinHeader_1x03_P2.54mm_Vertical
J8: Conn_02x04_Counter_Clockwise; PinHeader_2x04_P2.54mm_Vertical
RX: TestPoint; TestPoint_Pad_D1.5mm
TX: TestPoint; TestPoint_Pad_D1.5mm
U1: umft234xf_module; umft234xf
VBUS: TestPoint; TestPoint_Pad_D1.5mm
VIO: TestPoint; TestPoint_Pad_D1.5mm

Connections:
+5V: J1.16, J1.17, J4.1, J8.7, U1.5 (VBUS), VBUS.1
GND: GND.1, J1.3, J1.5, J1.6, J1.7, J1.9, J2.5, J3.2, J3.3, J5.1, J6.1, J7.1, J8.5, J8.6, U1.4 (GND)
GPIO1: J1.29, J7.2
GPIO2: J1.28, J5.2
GPIO6: J1.24, J6.2
unnamed: 3V3.1, U1.2 (3V3)
unnamed: CB0.1, U1.6 (CB0)
unnamed: J3.1, J4.3
unnamed: U1.3 (VIO), VIO.1
SPI_CLK: J2.4, J8.4
SPI_MISO: J2.2, J8.2
SPI_MOSI: J2.3, J8.3
Vdrive: J4.2, J5.3, J6.3, J7.3
iCE_RX: J1.10, TX.1, U1.7 (TXD)
iCE_TX: J1.11, RX.1, U1.9 (RXD)
~FLASH_CS: J2.1, J8.1
~RESET: J2.6, J8.8

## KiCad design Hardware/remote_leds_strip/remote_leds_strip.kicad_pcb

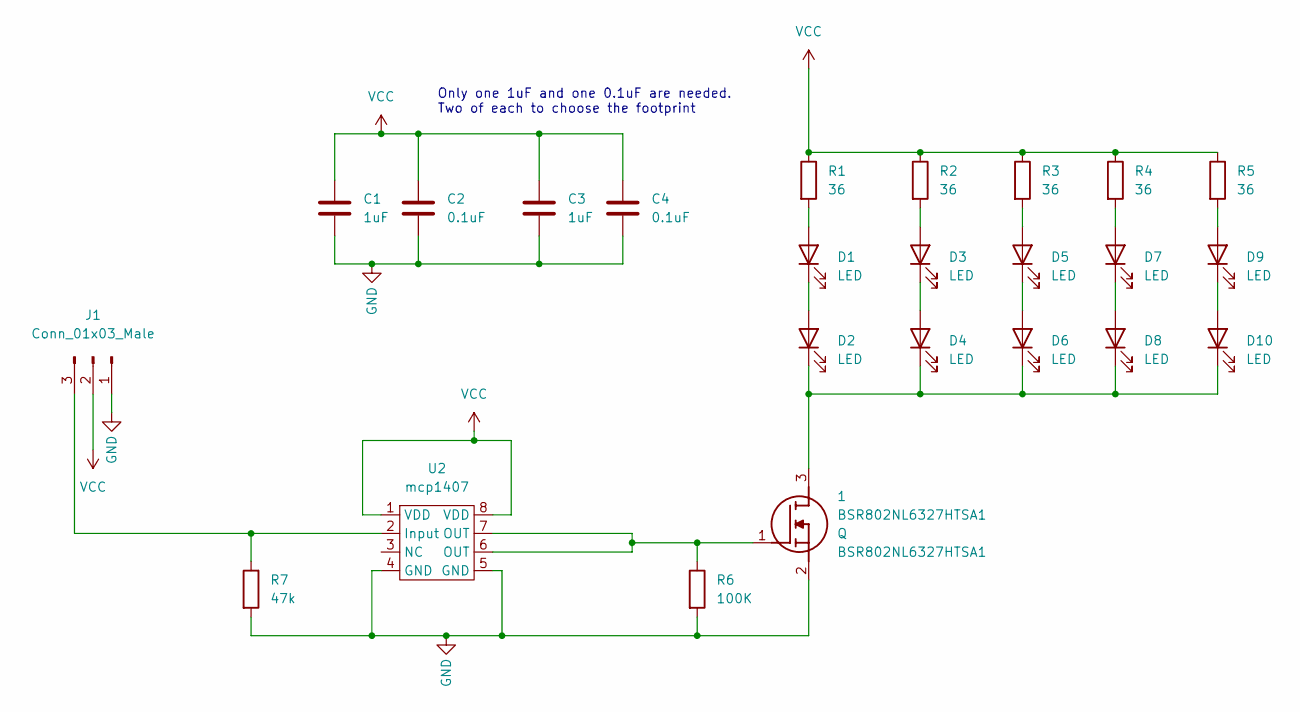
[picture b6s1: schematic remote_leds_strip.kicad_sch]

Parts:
1: BSR802NL6327HTSA1; SOT95P285X135-3N; Mouser Part Number 726-BSR802NL6327HTSA
C1: 1uF; C_0805_2012Metric_Pad1.18x1.45mm_HandSolder
C2: 0.1uF; C_0805_2012Metric_Pad1.18x1.45mm_HandSolder
C3: 1uF; CP_Radial_D5.0mm_P2.00mm
C4: 0.1uF; CP_Radial_D5.0mm_P2.00mm
D1, D2, D3, D4, D5, D6, D7, D8, D9, D10: LED; D_A-405_P2.54mm_Vertical_AnodeUp
J1: Conn_01x03_Male; PinHeader_1x03_P2.54mm_Vertical
R1, R2, R3, R4, R5: 36; R_0805_2012Metric_Pad1.20x1.40mm_HandSolder
R6: 100K; R_0805_2012Metric_Pad1.20x1.40mm_HandSolder
R7: 47k; R_0805_2012Metric_Pad1.20x1.40mm_HandSolder
U2: mcp1407; SOIC-8_3.9x4.9mm_P1.27mm

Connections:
GND: 1.2 (S), C1.2, C2.2, C3.2, C4.2, J1.1, R6.2, R7.2, U2.4 (GND), U2.5 (GND)
unnamed: D1.1 (K), D2.2 (A)
unnamed: D1.2 (A), R1.2
unnamed: D3.1 (K), D4.2 (A)
unnamed: D3.2 (A), R2.2
unnamed: D5.1 (K), D6.2 (A)
unnamed: D5.2 (A), R3.2
unnamed: D7.1 (K), D8.2 (A)
unnamed: D7.2 (A), R4.2
unnamed: D9.2 (A), R5.2
unnamed: 1.3 (D), D2.1 (K), D4.1 (K), D6.1 (K), D8.1 (K), D10.1 (K)
unnamed: D9.1 (K), D10.2 (A)
unnamed: J1.3, R7.1, U2.2 (Input)
unnamed: 1.1 (G), R6.1, U2.6 (OUT), U2.7 (OUT)
VCC: C1.1, C2.1, C3.1, C4.1, J1.2, R1.1, R2.1, R3.1, R4.1, R5.1, U2.1 (VDD), U2.8 (VDD)

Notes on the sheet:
Only one 1uF and one 0.1uF are needed. Two of each to choose the footprint

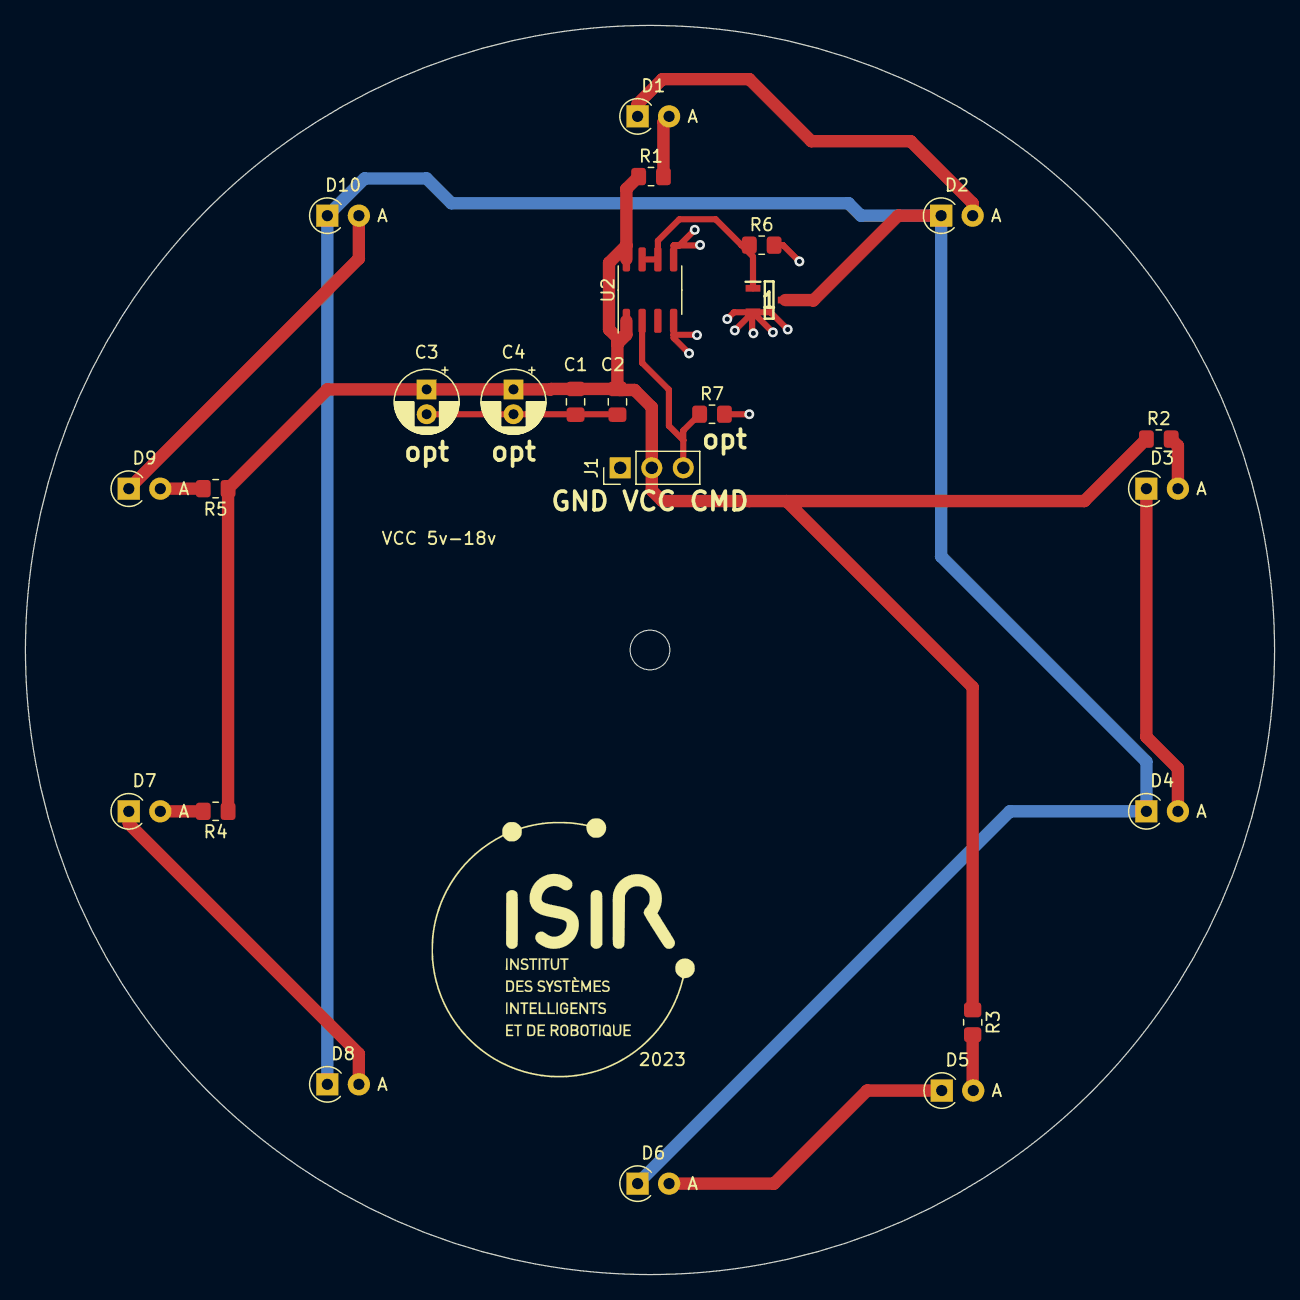
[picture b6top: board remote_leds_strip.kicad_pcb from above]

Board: 2 copper layers, 100.7 x 100.7 mm, 24 parts (0 on the bottom side), 15 nets.
